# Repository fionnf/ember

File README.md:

# Ember

Two Raspberry Pi Pico W boards keeping their SK6812 RGBW LED strips in sync over MQTT. Touch one lamp and both shift colour together. Control everything from a web app that works on any phone or browser.

---

## Overview

```
[Web UI] ──MQTT (WebSocket)── [board_a / BOSS] ──sync── [board_b / follower]
                                SK6812 strip               SK6812 strip
```

One board (`board_a`, display name **A**) is the BOSS; the other (`board_b`, **B**) is the follower. Both subscribe to the same MQTT topic and keep their strips in sync. The web UI publishes JSON commands to the same topic and reflects live state from both boards.

---

## Hardware

| Part | Notes |
|------|-------|
| Raspberry Pi Pico W (×2) | The W variant — needs WiFi |
| SK6812 RGBW LED strip | 10 LEDs per board, GRBW byte order |
| Data pin | GPIO 5 |
| 300–470 Ω resistor | Series on DIN — prevents ringing |
| 5 V power supply | USB or direct to strip |

### Wiring

```
Pico W GPIO 5 ──[330Ω]──── DIN ────────────── DOUT
5 V / 3.3 V   ─────────── VCC
GND           ─────────── GND

Pico W TOUCH_PIN ──┬──── copper pad / foil
                   └─[1MΩ]── GND
```

> Data flows DIN → DOUT; connect the board's data wire to the **DIN** end of the strip.

If board B connects via the far end (DOUT side), set `REVERSE_LEDS = True` in `config.py` to flip group order in software.

---

## Firmware

### Files

| File | OTA-updated | Purpose |
|------|-------------|---------|
| `boot.py` | Never | OTA bootstrap — downloads firmware from GitHub on every boot |
| `main.py` | Yes | Main loop: WiFi, MQTT, touch, alarms, BOSS sync |
| `colour.py` | Yes | Colour engine: groups, fades, breathing, drift |
| `sk6812.py` | Yes | PIO-based SK6812 RGBW driver |
| `touch.py` | Yes | Capacitive touch detection |
| `config.py` | Never | Per-board constants (never overwritten by OTA) |

### OTA Updates

`boot.py` runs before `main.py` on every boot. It connects to WiFi and downloads the latest `main.py`, `colour.py`, `sk6812.py`, and `touch.py` from the `master` branch of this repo. `config.py` and `boot.py` are never touched. If WiFi is unavailable the board boots from whatever is already on flash.

To update both boards: commit and push to `master`, then click **↺ Reboot Both Boards** in the Settings panel.

Updates are **all-or-nothing**: every file is downloaded and compile-checked before any is installed, so a mid-update network drop can't leave a new `main.py` running against an old `colour.py`.

### Crash-loop rollback

The compile gate rejects firmware that doesn't parse, but valid code can still fail at runtime — a stray function-level `import` once shadowed a module-level one and both boards boot-looped, unreachable until a human pushed a fix. So the boards now keep a way back:

1. `boot.py` increments a counter in `bootfail.txt` on every boot. A **power-on** reset doesn't count — only soft and watchdog resets, which is what a crash loop produces.
2. Once `main.py` has run for a minute it calls `mark_stable()`: the counter is cleared and the running files are promoted to `.ok` backups. Backups are only rewritten when they actually differ, so this costs no flash in steady state.
3. After **3** boots that never reach stability, `boot.py` restores the `.ok` set and skips the update for that one boot — otherwise it would immediately reinstall the firmware that was failing. The lamp comes back on its own in about 15 seconds.
4. The board reports `rolled_back: true` in its heartbeat until it is stable again, so a rejected push is visible rather than silent.

No record is kept of the rejected version: the next scheduled reboot re-downloads `master`, so a pushed fix is picked up with no stale state to clear, and a few quick power cycles can't pin a board to old firmware.

> `boot.py` is **never** updated over the air — a broken bootloader would need USB to recover. Copy it to each board manually once to get this feature (`mpremote connect /dev/ttyACM0 cp boot.py :`).

### Configuration (`config.py`)

```python
BOARD_ID   = "board_a"    # "board_b" on the second Pico
BOSS       = True         # True on board_a only

NUM_LEDS       = 10
LED_PIN        = 5
REVERSE_LEDS   = False

NUM_GROUPS     = 3
GROUP_MIN_LEDS = 1
GROUP_MAX_LEDS = 8

LED_BRIGHTNESS = 0.6
FADE_STEPS     = 60       # steps per colour transition (~1 s at 60 Hz)
BREATHE_SPEED  = 0.0008   # radians/ms
BREATHE_DEPTH  = 0.04     # ±4% brightness oscillation

IDLE_DRIFT_INTERVAL_S = 45

MQTT_BROKER        = "broker.hivemq.com"
MQTT_PORT          = 1883
MQTT_TOPIC_PREFIX  = "ember_CHANGEME"   # ← set to your own unique value

WIFI_NETWORKS = [
    ("YourSSID", "YourPassword"),
]
```

### MQTT

- **Broker:** `broker.hivemq.com:1883` (TCP on device) / `:8884` WSS (web)
- **Events topic:** `<your-prefix>/events`
- **Alarms topic:** `<your-prefix>/alarms` (retained, subscribed by boards)
- **Status topic:** `<your-prefix>/status/<board_id>` (retained, Last-Will)
- **Scenes topic:** `<your-prefix>/scenes` (retained, client-to-client scene library)

All messages are JSON with a `from` field for echo suppression. The full contract is documented in [MQTT Protocol Specification](#mqtt-protocol-specification) — that section is the reference for writing an additional client.

### Colour Engine (`colour.py`)

The `ColourEngine` class manages per-group colour state:

- **Palette position** (`pos`, float 0.0–1.0): maps into a 30-stop hue palette blended with warm white. `0.0` = pure warm white (W channel only); higher values = saturated hues with W fading out.
- **Groups**: the strip is split into 1–N independent colour zones. Each group has a `pos` (hue) and a `w` (warm-white level). Group sizes are stored separately.
- **Fade**: each group independently crossfades from its start colour to its target over `FADE_STEPS` ticks, eased with smoothstep so the transition begins and ends imperceptibly. A fade takes the time it says it does — `fade_steps: 60` really is ~1 s.
- **Breathing**: a per-group sine oscillator adds a slow ±4% brightness pulse with staggered phases.
- **Drift**: optional autonomous colour drift — subtle hue nudges and group-size shifts every `IDLE_DRIFT_INTERVAL_S` seconds. Disabled by default in the web UI (`driftEnabled = false`).
- **Power**: soft on/off with an ~800 ms fade.

### BOSS / Follower Sync

When the BOSS's physical touch sensor fires, it runs `ColourEngine.impulse()` (random colour change), then publishes its new state with `"sync": true`. The follower applies the same groups with a fast fade (`SYNC_FADE_STEPS`) so both strips match immediately.

Every 60 s the BOSS publishes its state with `"sync": true` as a drift-correction heartbeat. The follower applies it with a slow 300-step fade so re-alignment is invisible.

**Independent mode.** That periodic sync would otherwise undo deliberate per-lamp settings — set one lamp with **Send to → B** and it reverted within a minute. So a **targeted** command (one carrying `target`) unlinks the lamps and suppresses the BOSS sync for 30 minutes; a **broadcast** colour command — which sets both lamps to the same thing — re-links them immediately. Boards notice targeted traffic even when it is addressed to the other lamp, so the BOSS knows to stand down.

### Alarms

Each board holds the whole schedule on its own flash (`alarms.json`) and evaluates it against its own clock, so **alarms fire with no client connected**. On each main-loop tick the board compares the current UTC time against enabled alarms and runs:

- **Sunrise** (`type: "sunrise"`): switches on and ramps brightness from 0 to `alarm.brightness` over `duration_min` minutes, sweeping **colour** alongside it — ember red → deep orange → amber → warm white. Because brightness rises together with the colour, the early stops are seen dim and deep, like a real dawn.
- **Bedtime** (`type: "sunset"`): the same sweep in reverse — warm white deepens to ember as it dims — then switches off (restoring the previous brightness so the next power-on isn't dark).

The gradient is `SUNRISE_STOPS` in `colour.py`, deliberately **not** taken from `TINT_PALETTE`: there a single `pos` sets hue and saturation together, so anything warm is also nearly white and a dawn would be an invisible tint.

Stops are evenly spaced by index, so where they sit is what shapes the fade. They are weighted toward the red end: the dawn opens on near-pure red `(255,6,0,0)`, the white LED stays completely dark for the first three fifths, and the turn to warm white happens in the last stretch. Red is never given up — the R channel is full the whole way — so it lands on a warm white with red still under it rather than a cold one. `tests/test_sunrise.py` pins that shape, so the stops stay tunable but the character can't drift back to turning orange almost immediately.

The schedule reaches boards two ways: the **retained** `P/alarms` topic, which boards subscribe to so an offline or rebooting board picks it up on reconnect, and a `set_alarms` message on `P/events` for boards that are already online. Alarms are compared in **UTC**; clients convert local time. See the [protocol spec](#alarms-1) for the exact format.

Two requirements: the board needs a **synced clock** (NTP at boot, retried hourly — the heartbeat's `ntp` field reports this, and the web UI warns when it's false), and it needs to have **received the schedule** (the heartbeat's `alarms` count confirms it). Use the **▶ Test** button on any alarm to run its fade immediately and verify the whole path.

### WiFi Watchdog

If the board loses its MQTT connection (WiFi down or broker unreachable) for more than 10 minutes (`WIFI_OFFLINE_REBOOT_MS = 600000`) it reboots to reconnect and pick up any OTA update. Known networks are the `WIFI_NETWORKS` list in `config.py` plus any saved to `networks.json` on flash, tried in order.

### State Persistence

On/off state and brightness are written to `state.json` and restored on boot before connecting to MQTT — so the lamps come back exactly as they were after the nightly OTA reboot.

Writes are deliberately rationed. The web app includes `on` in every state publish, so persisting on each message meant a flash erase/write on every slider tick (~8 per second while dragging) — needless wear, and each write stalls the render loop. State is now written only when it actually changes: immediately on a power toggle, before any planned reboot, and on a 5-minute flush that bounds what an unexpected power cut can lose.

### Daily OTA reboot

Each board reboots once a day at **17:00 UTC** (`OTA_HOUR_UTC` in `main.py`) to pull the latest firmware. State (on/off + brightness) is saved before the reboot and restored after, so the lamps come back as they were.

### Resilience layers

The firmware is designed to recover from anything without human intervention:

| Layer | Failure it handles |
|-------|--------------------|
| Hardware watchdog (8 s) | Firmware *hangs* — stuck DNS, dead socket, lockup → automatic reboot |
| Crash guard | Any unhandled exception → reboot in 5 s, OTA pulls a fix on the way up |
| OTA compile check | A broken push to master, truncated download, or HTML error page is **refused** — boards keep running the last good firmware |
| All-or-nothing OTA | Every file is downloaded and verified before *any* is installed, so a mid-update network drop can't leave a new `main.py` running against an old `colour.py` |
| Flash-write rationing | State is written only when it changes, so slider drags can't wear out the flash |
| Atomic file writes | Power cut mid-write can't corrupt firmware or state/alarm/network files |
| MQTT input validation | The events topic is on a public broker — every field is validated and clamped before touching the engine or flash; malformed messages are logged and dropped |
| MQTT watchdog | Broker unreachable > 10 min → reboot to re-establish everything |
| NTP retry | Failed clock sync at boot retries hourly (otherwise alarms would silently stay dead until the next reboot) |
| State persistence | On/off + brightness restored after any reboot |
| Periodic GC | Heap stays defragmented over weeks of uptime; free memory is reported in every heartbeat |

The watchdog can be disabled per board (`WATCHDOG_ENABLED = False` in `config.py`) while debugging over WebREPL.

---

## Web UI

`index.html` at the repo root is served via **GitHub Pages**. It connects to the HiveMQ broker over WebSockets. No install required — open it in any browser. On a phone you can **Add to Home Screen** to get it as a standalone full-screen app (web manifest included), and the app automatically reconnects when you return to it after backgrounding.

A service worker (`sw.js`) caches the app shell and the mqtt.js library, so the UI keeps working if the CDN is unreachable. HTML is fetched network-first, so a pushed update always lands rather than stranding you on a cached build.

### Controls

| Control | What it does |
|---------|-------------|
| **Power** | Soft on/off; state reflected in board pills immediately |
| **Tap** | Random colour change (same as physically touching the lamp) |
| **Warm White** | Resets all groups to `pos=0.0, w=1.0` (pure warm white) |
| **Brightness** | Global brightness 0–100% |
| **Fade Speed** | Colour transition duration (~0.3 s–10 s) |
| **Send to** | Target Both boards / A only / B only |

### Strip preview

The top card shows the RGBW strip in real time. Click the small divider cells below the strip to split or merge colour groups.

### Groups

Each group gets a numbered handle on the palette bar — drag it along the hue gradient to pick a colour. The **Warm White** slider below each group blends in warm white independently.

### Alarms

Create sunrise/bedtime alarms per lamp with day-of-week selection, duration, and target brightness.

Times are entered in **your local time**; the small `HH:MM UTC` hint beside each one shows what the lamps actually compare against. Because the firmware only knows UTC, the app stores your intended local time and recomputes the UTC value when needed, so an alarm set for 07:00 stays at 07:00 after a daylight-saving change.

Each alarm has a **▶ Test** button that runs its fade on both lamps immediately (20 s) — the quickest way to confirm the whole path works. A warning banner appears if a lamp's clock hasn't synced, since alarms can't fire without it.

### Scenes

Save and load complete lamp states (colours, group layout, brightness, fade speed).

Scenes are stored in `localStorage` **and** mirrored to the retained `P/scenes` topic, so your phone, your laptop and any other client converge on one shared library. The merge is deliberately conservative — no device can destroy another's work:

- scenes merge by `id`, keeping whichever copy has the newer `updated` stamp
- a scene simply missing from another device's list means "not seen yet", never "delete it"
- deletions travel as **tombstones**, so a deleted scene isn't helpfully synced back by a device that still has it (kept to the last 50)

### Settings panel

| Field | Default | Description |
|-------|---------|-------------|
| WebSocket URL | `wss://broker.hivemq.com:8884/mqtt` | MQTT broker |
| Topic Prefix | randomly generated per install | Must match `MQTT_TOPIC_PREFIX` on the boards |
| LEDs | `10` | LEDs per strip |
| Groups | `3` | Initial group count |

Also: **Add WiFi Network** (sends credentials to both boards over MQTT), **↺ Reboot Both Boards** (triggers OTA update).

### Board presence pills

The two pills (A / B) at the top right show each board's status. Presence uses MQTT **Last-Will** on a retained per-board topic (`prefix/status/<board_id>`): each board publishes `{"online": true}` (retained) on connect, and the broker itself flips it to `{"online": false}` if the board dies silently (within ~90 s of its last keepalive). Because the status is retained, the pills are correct the instant the page loads. The web app additionally pings both boards on connect and every 2 minutes to refresh their full state.

- **Green (online)** — retained status online (or message seen within 150 s) and lights on
- **Amber (standby)** — same, but lights are off
- **No highlight (offline)** — broker reported the board offline, or nothing heard within 150 s

---

## MQTT Protocol Specification

This is the complete contract. Any client (this web app, another web app,
Home Assistant, a script) only needs these topics — there is no other API.

### Topics

With your `MQTT_TOPIC_PREFIX` (call it `P`):

| Topic | Direction | Retained | Payload |
|-------|-----------|----------|---------|
| `P/events` | client ⇄ board | no | Command / state object (below) |
| `P/alarms` | client → board | **yes, QoS 1** | Bare JSON **array** of alarm objects |
| `P/status/<board_id>` | board → client | **yes** | `{"online": bool, "fw": str, "ntp": bool}` |
| `P/scenes` | client ⇄ client | **yes** | Shared scene library (below). Boards ignore it entirely |

Board IDs are `board_a` (BOSS, display name A) and `board_b` (follower, B).

A client should subscribe to `P/events`, `P/alarms`, and `P/status/+`.

### Message envelope (`P/events`)

Every message on `P/events` is a JSON **object**. Non-objects are dropped.

| Field | Type | Meaning |
|-------|------|---------|
| `from` | string | **Required.** Sender ID. A board ignores messages where `from` equals its own ID. IDs starting with `board_` mark board-to-board traffic |
| `target` | string | Optional. If present, only the board with this `board_id` acts on the message |
| `echo` | bool | Optional. Marks an informational state report. **Boards ignore echo-flagged messages** — see below |
| `sync` | bool | Optional. Board-to-board: apply colours with a slow 300-step fade |

> **The `echo` rule matters.** When a board answers a client, it replies with
> its full state plus `"echo": true`. Without that flag the *other* board
> would treat the reply as a real colour change and restart its fade — which
> caused a visible flash on every interaction. If you write a client, never
> set `echo` on commands you send; treat incoming `echo` messages as
> read-only state.

### Commands (client → board, on `P/events`)

All fields are optional; send only what you want to change. Every value is
validated and clamped by the firmware — out-of-range or wrong-typed fields
are ignored, never fatal.

| Field | Type | Range | Effect |
|-------|------|-------|--------|
| `groups` | array | 1…`NUM_LEDS` entries | Per-group colour, below |
| `on` | bool | | Power, with an ~800 ms soft fade |
| `brightness` | number | 0.0–1.0 | Global brightness |
| `fade_steps` | number | 1–2000 | Crossfade length in ~16 ms ticks (60 ≈ 1 s) |
| `drift_enabled` | bool | | Autonomous idle colour drift |
| `drift_interval` | number | 5–86400 | Seconds between drift events |
| `reverse` | bool | | Flip LED order |
| `ping` | any | | Ask boards to reply with their state (`echo: true`) |
| `set_alarms` | array | ≤20 alarms | Install a schedule (see Alarms) |
| `test_alarm` | `"sunrise"` \| `"sunset"` | | Run that fade **immediately** |
| `test_seconds` | number | 2–600 | Duration for `test_alarm` (default 20) |
| `add_network` | object | | `{"ssid": str≤32, "password": str≤64}` — saved to the board's flash |
| `reboot` | truthy | | Save state and restart (triggers an OTA check) |

A `groups` entry:

```json
{"pos": 0.35, "w": 0.8, "size": 3}
```

| Field | Type | Range | Meaning |
|-------|------|-------|---------|
| `pos` | number | 0.0–1.0 | Position in the hue palette. `0.0` = pure warm white (W channel only); higher = saturated tint with W fading out |
| `w` | number | 0.0–1.0 | Warm-white level for this group |
| `size` | integer | ≥1 | How many consecutive LEDs this group covers |

`size` values should sum to `NUM_LEDS`. If they sum to less, the firmware
extends the last group to cover the remainder (so no LED is left showing a
stale colour); if they sum to more, the extra is trimmed. The firmware
resizes its internal group arrays to match the array length, so a per-LED
gradient is simply `NUM_LEDS` groups of `size: 1`.

Example — set three groups and full brightness:

```json
{
  "from": "my_app",
  "groups": [
    {"pos": 0.0,  "w": 1.0, "size": 4},
    {"pos": 0.35, "w": 0.8, "size": 3},
    {"pos": 0.7,  "w": 0.6, "size": 3}
  ],
  "on": true,
  "brightness": 0.6,
  "fade_steps": 60
}
```

### Reports (board → client, on `P/events`)

**State echo** — sent whenever a board acts on a client message (including `ping`):

```json
{
  "from": "board_a", "echo": true,
  "groups": [{"pos": 0.0, "w": 1.0, "size": 10}],
  "on": true, "brightness": 0.6, "fade_steps": 60,
  "drift_enabled": false, "drift_interval": 45
}
```

**Heartbeat** — every 30 s:

```json
{"from": "board_a", "heartbeat": true, "fw": "2026-07-26.5",
 "mem": 102400, "ntp": true, "alarms": 2}
```

| Field | Meaning |
|-------|---------|
| `fw` | Firmware version |
| `mem` | Free heap bytes — watch for leaks |
| `ntp` | **Clock synced?** If `false`, alarms cannot fire — surface this to the user |
| `alarms` | How many alarms the board currently holds — confirms delivery |

**Impulse / boss sync** — a physical touch, or the BOSS's 60 s sync. Same
shape as a state echo but **without** `echo`, so the other board applies it.
Boss syncs carry `"sync": true`.

### Presence (`P/status/<board_id>`, retained)

```json
{"online": true, "fw": "2026-07-26.5", "ntp": true}
```

Registered as the board's MQTT **Last-Will** with payload `{"online": false}`,
so the *broker* publishes the offline state if a board dies silently
(~90 s, from the 60 s keepalive). Because it is retained, a client knows both
boards' state the instant it subscribes — no waiting for a heartbeat.

Recommended client logic: treat `online: false` as authoritative offline;
otherwise consider a board present if `online: true` or a message arrived
within ~150 s. Show offline if your own broker connection is down.

### Alarms

Two transports, both needed:

1. **`P/alarms`, retained, QoS 1** — the durable schedule. Boards subscribe
   to it, so one that was offline or rebooting when the schedule changed
   receives it on reconnect. Payload is a bare JSON **array**.
2. **`{"set_alarms": [...]}` on `P/events`** — the instant path for boards
   that are already online.

Publish **both** on every change, and **never** set `target` on an alarm
update: which lamp acts is decided by the alarm's own `boards` field.

```json
[
  {
    "enabled": true,
    "type": "sunrise",
    "hour": 5,
    "minute": 0,
    "duration_min": 30,
    "brightness": 1.0,
    "days": [0, 1, 2, 3, 4],
    "boards": ["board_a", "board_b"]
  }
]
```

| Field | Type | Range | Meaning |
|-------|------|-------|---------|
| `enabled` | bool | | Skipped when false |
| `type` | string | `sunrise` \| `sunset` | Fade up, or fade down and switch off |
| `hour` | int | 0–23 | **UTC** — see below |
| `minute` | int | 0–59 | **UTC** |
| `duration_min` | int | 1–180 | Ramp length in minutes |
| `brightness` | number | 0.0–1.0 | Sunrise target (ignored for sunset) |
| `days` | int array | 0=Mon … 6=Sun | Omit or send a non-array for *every day* |
| `boards` | string array | board IDs | Which lamps act. Empty/omitted = all |

Each board evaluates the schedule against **its own** UTC clock and runs its
own ramp, so alarms work even with no client connected. At most one alarm
fires per minute per board; a fired alarm is remembered until the next day
(keyed on hour+minute+type, so a sunrise and a sunset at the same time both
fire).

> **Timezone.** The Pico has no timezone database, so the firmware only
> understands UTC. Clients are responsible for converting. This web app edits
> in local time and stores the user's intent in two extra fields, `lh`/`lm`
> (local hour/minute), recomputing `hour`/`minute` on load so alarms keep
> their wall-clock time across a DST change. The firmware ignores `lh`/`lm`.
> **If you write another client, either use the same convention or send UTC
> directly** — and be aware this app will rewrite `hour`/`minute` from
> `lh`/`lm` if both are present.

To verify a schedule without waiting for the clock, send
`{"from": "my_app", "test_alarm": "sunrise", "test_seconds": 20}` — the
board runs the real alarm code path immediately.

### Scenes (retained on `P/scenes`)

Boards ignore this topic entirely; it exists so multiple clients share one
scene library. Publish **retained** so a client that connects later gets it.

```json
{
  "v": 1,
  "from": "web_app",
  "scenes": [
    {
      "id": "lz4f8x-a91b2c",
      "updated": 1774598400000,
      "name": "Evening",
      "groups": [{"pos": 0.0, "w": 1.0, "size": 10}],
      "boundaries": [], "groupPositions": [0.0], "groupWLevels": [1.0],
      "brightness": 0.4, "fadeSteps": 120, "on": true
    }
  ],
  "deleted": ["old-scene-id"]
}
```

| Field | Meaning |
|-------|---------|
| `id` | Stable unique string. **Required** for a scene to take part in sync |
| `updated` | Epoch ms of the last edit — the conflict tiebreak |
| `deleted` | Tombstoned ids, capped at the most recent 50 |

Merge rules (implement these and two clients can't fight):

- union by `id`; on a clash keep the higher `updated`
- a scene absent from the other side means "not seen yet", **not** "delete"
- honour incoming tombstones, and keep publishing your own so a delete
  doesn't get synced back by a device that still holds the scene
- if the merge changed nothing, don't republish — otherwise two clients
  ping-pong retained messages forever

Everything except `id`, `updated` and `name` is opaque payload; this app
stores the fields shown, but another client may store whatever it needs.

### Guarantees for client authors

- Malformed messages are logged and dropped; they never crash a board or
  drop its MQTT connection.
- Unknown fields are ignored, so the protocol can be extended safely.
- Boards persist power state, brightness, and alarms to flash and restore
  them after any reboot.
- The events topic is on a **public broker**. Anyone who knows your prefix
  can control your lamps — pick an unguessable `MQTT_TOPIC_PREFIX`, or run
  your own broker with authentication.

---

## First-Time Setup

1. **Flash MicroPython** — download the Pico W UF2 from micropython.org, hold BOOTSEL, drag it on.

2. **Install umqtt** (in Thonny shell or `mpremote`):
   ```python
   import mip
   mip.install("umqtt.simple")
   ```

3. **Upload files** (only once):
   ```bash
   mpremote connect /dev/ttyACM0 cp boot.py config.py :
   ```
   Set your WiFi credentials in `WIFI_NETWORKS` in the board's `config.py`
   (or create `networks.json` on the board — a list of `[ssid, password]` pairs):
   ```json
   [["YourNetwork", "YourPassword"]]
   ```

4. **Edit `config.py`** — set `BOARD_ID`, `BOSS`, `NUM_LEDS`, `LED_PIN`, `MQTT_TOPIC_PREFIX`.

5. **Reboot** — `boot.py` downloads `main.py`, `colour.py`, `sk6812.py`, `touch.py` from master and starts.

---

## Troubleshooting

| Symptom | Cause | Fix |
|---------|-------|-----|
| Board B LEDs don't light | Connected to DOUT | Run wire to DIN end |
| Wrong colours | Byte-order mismatch | SK6812 uses GRBW — check `sk6812.py` |
| Groups reversed on board B | Far-end connector | `REVERSE_LEDS = True` in `config.py` |
| Touch never fires | Threshold too high | Lower `TOUCH_THRESHOLD` in `config.py` |
| Touch fires constantly | Missing pull-down | 1 MΩ between GPIO and GND |
| Boards not syncing | Different topic prefix | `MQTT_TOPIC_PREFIX` must match on both |
| Board reboots after ~10 min offline | WiFi watchdog | Expected; board reconnects and checks OTA |
| **Alarm fires at the wrong time** | Alarm times are UTC; older clients sent local time as UTC | Times are now edited in local time and converted. Check the small `HH:MM UTC` hint next to each alarm |
| **Alarm never fires** | Board has no clock (NTP failed) | The web UI shows a warning banner; heartbeat `ntp` is false. Retries hourly, or reboot the board |
| **Alarm never fires**, clock is fine | Board never received the schedule | Heartbeat `alarms` count shows 0. Fixed by the retained `P/alarms` topic; press **▶ Test** to confirm the path |
| Alarm only fires on one lamp | Alarm's `boards` list, or a client sending `target` with the update | Enable both lamps on the alarm; never set `target` on alarm updates |
| OTA not updating | `boot.py` not on board | Flash `boot.py` manually once via USB |

---

## Project Structure

```
ember/
├── index.html              # Web UI — single source, served by GitHub Pages
├── sw.js                   # Service worker — caches shell + mqtt.js
├── manifest.json           # PWA manifest (Add to Home Screen)
├── main.py                 # Firmware — main loop (OTA-fetched)
├── colour.py               # Firmware — colour engine (OTA-fetched)
├── sk6812.py               # Firmware — PIO LED driver (OTA-fetched)
├── touch.py                # Firmware — capacitive touch (OTA-fetched)
├── boot.py                 # OTA bootstrap (deployed manually, never overwritten)
├── config.py               # Per-board config TEMPLATE — real credentials live
│                           #   only on the boards, never in the repo
├── hardware_test.py        # Standalone wiring test (no WiFi/MQTT needed)
├── favicon.svg
└── README.md
```

> **Security note:** this repo is public (it serves the web UI via GitHub Pages).
> Never commit real WiFi or WebREPL passwords — edit them only in the `config.py`
> that lives on each board, which OTA never touches.

---

Personal project — no license.

---

## Tests

```bash
python3 tests/test_firmware.py     # boots main(), MQTT commands, flash writes
python3 tests/test_ota.py          # OTA all-or-nothing install
python3 tests/test_rollback.py     # crash-loop rollback
python3 tests/test_sunrise.py      # dawn gradient shape
node    tests/test_scene_sync.js   # scene merge / tombstone rules
```

Runs `main()` against stubbed MicroPython modules (`tests/stubs/`) and checks
that the board boots, arms and feeds the watchdog, subscribes to the events
**and** retained alarms topics, registers its Last-Will, publishes presence and
heartbeats, reboots on command, installs a retained alarm schedule, applies
colour commands, and survives malformed input.

`test_ota.py` drives `boot.py`'s updater against a stubbed HTTP layer and
asserts that a network drop, a syntax error, or an HTTP error part-way
through leaves the existing firmware completely untouched.

Run both before pushing to `master`. `python -m py_compile` only catches syntax
errors — it cannot catch a runtime fault such as a stray function-level
`import`, which once shadowed a module-level import for the whole of `main()`
and put every board into a boot loop.

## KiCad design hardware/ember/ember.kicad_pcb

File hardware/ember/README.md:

# EM-15 rev I — KiCad project

**Ember · EM-15 rev I · © 2026 Fionn Ferreira**
<https://github.com/fionnf/ember>

Generated from [`../../docs/hardware/README.md`](../../docs/hardware/README.md).
Open `fl11.kicad_pcb` with KiCad 9 or 10.

## What changed

**rev B** moved the electronics off the end of the strip into a rear bulge at the middle, so
the USB-C plugs in from the back. **rev C** moved the touch terminals there too: the pad is
now a snap-off section *beside* the bulge, not a tab at the far end.

```
   x=0                                              187
   |<---------- 11 x SK6812 RGBW, unbroken --------->|
   +--------------------------------------------------+
   | (1)(2)(3)(4)(5)(6)(7)(8)(9)(10)(11)  y = 11.000  |
   +----------------+--------------+---+--------------+
        y=20        |  ELECTRONICS |sn |  TOUCH PAD   |
                    |  MCU, power  |ap |  PAD_S       |
                    |  USB-C under |   |  PAD_G       |
              x=72  +--------------+---+--------------+ x=145
                         y=48    x=120 (break + J2/J3)
```

Every wire now leaves the lamp from one place. The board also got **smaller**:

| | rev A | rev B | rev C |
|---|---|---|---|
| Outline | 282 × 20 | 228 × 20 + 48 × 28 | **187 × 20 + 48 × 28 + 25 × 28** |
| Area | 5640 mm² | 5904 mm² | **5784 mm²** (+2.6 % vs A, −2.0 % vs B) |
| SENSE run | 195 mm | ~70 mm | **~13 mm** |
| SENSE crosses the LED data channel | no | yes, once | **no** |

**The real win is SENSE.** §7.5 calls touch "the least-certain subsystem in this design". In
rev A and B the sense line was a long high-impedance run down a strip carrying a 0.89 A
switching rail. In rev C it never leaves the bulge, sits inside the bulge's GND pour — which
*is* the guard — and never crosses the LED data channel. The guarded y=18.6 lane rev B needed
is gone entirely, and so is the awkward climb at x=188.

Deleting the end tab also removed the 31 mm tab, the gap, and the strip's break slot.

**Cost.** Still one bottom-side part (J1), so the second-setup charge stands at roughly
**+$0.63/unit at qty 100**. The outline is a T with a notch, so the 6-up panel still needs
re-nesting and re-quoting.

## rev I — TTP223 module, and the etched sensor is gone

The biggest simplification in the whole design. A **TTP223-class module plugs into J4**
(pin order **IO / VCC / GND**) and does the sensing, which deletes:

- the etched comb electrodes and their whole geometry problem
- the snap-off pad section, the break line, the webs and both bridges
- R10's 4.7 MΩ (now 100 k, a value already on the BOM) — **the thinnest-stock line is gone**
- §7.5's entire uncertainty: the charge-time measurement, the per-unit threshold question,
  the overlay-thickness dependence, the "least-certain subsystem in this design" note

`touch.py` becomes a digital read instead of a timing loop.

**VCC is 3V3, not 5V, deliberately.** These modules drive their output rail-to-rail and the
ESP32-C3 is **not 5V tolerant** (3.6 V absolute max). At 3V3 the output is inherently safe,
and R7's 5.1 kΩ stays in series as belt and braces. `TS3/TS4/TS5` repeat the same three
signals as solder terminals for when no JST housing is to hand.

**Centred geometry.** The LED row sits square on the strip — **15.567 mm of headroom at each
end**, identical. The USB-C sits **dead centre of the bulge at x=98.0**; the module moved
aside to x=115 to make room, which puts its antenna keep-out at y 40.9–46.3 facing the free
y=52 edge, **23.9 mm** from the nearest LED copper against a rule of 8.

**Four screws**: two in the bulge, and one at **each end of the LED strip**, so the full
length is held down rather than just the electronics.

### Routing: complete

| | |
|---|---|
| **Unconnected component pads** | **0** |
| DRC errors | **0** |
| Board | 187 × 20 strip + 64 × 32 bulge, single-sided, 2 layer |
| BOM | 16 lines, 59 placements, 5 BASIC |

Pipeline: `build_fl11.py` places and netlists, `route_fl11.py` lays the pours and the nets
§7.9 insists on by hand, freerouting 2.3.0 finishes the rest through KiCad's Specctra
DSN/SES path, and `finish_routing.py` cleans up after it — width floor, 133 collision-checked
ground vias, solid ties, island removal, stray-pad joins.

## rev G — 15 LEDs, fully routed

**15 LEDs at 11.13333 mm pitch.** The lit zone stays at exactly **167.00 mm** — the lamp
length does not move — and worst-case current drops to **~1.69 A**, back under the 2 A PPTC
hold and inside a 2.4 A supply. F1 returns to the 2 A/4 A part. Both of the warnings rev F
carried (3 A supply, copper resized for 2.25 A) are withdrawn: at 1.69 A the §5.5 sizing
holds with margin.

**The LEDs are warm white.** `C5378724` is `SKC6812RGBW-**WS**` — the WS suffix is warm white.
The neutral-white part is `C5348912` (`-NW`) and would fight `BASE_WARM_WHITE = (0,0,0,200)`,
which is the whole basis of `colour.py`'s model. The BOM note says so explicitly.

### Routing: complete

| | |
|---|---|
| **Unconnected component pads** | **0** |
| DRC errors | 2 (below) |
| Tracks / vias | 345 / 202 — 279 on F.Cu, 66 on B.Cu |
| Copper routed | 865 mm |
| SENSE vias | **0**, as §7.1 requires |

The bulge was finished with **freerouting 2.3.0** driven through KiCad's Specctra DSN/SES
path, then post-processed by `finish_routing.py`. §7.9 says not to autoroute, and that stands
for the three nets it names — so SENSE, the LED chain, the tab bridges and the pours were
hand-routed **first** and the router had to work around them. It did: SENSE still has zero
vias and still never crosses the LED data channel.

`finish_routing.py` then does what the router got wrong: widens its 0.15 mm tracks to the
0.20 mm floor, stitches the ground pours to the plane with 146 collision-checked vias, ties
the priority-3 solid patches that the pour clips around, and removes floating copper islands.

### The two remaining DRC errors — both need a human

1. **`J1.A6` (USB_DP_CONN) vs a USB_DM_CONN track.** This is the 0.5 mm-pitch USB-C fan-out,
   where D+ and D− interleave (`B7 · A6 · A7 · B6` at 0.5 mm). Untangling it needs either a
   via pair under the connector or hand-drawn geometry; it is exactly the case §6.2 means when
   it says route D± by hand.
2. **A STRAP2 via vs a +3V3 track.** A router artifact, a local nudge in KiCad.

Neither is a connectivity failure — every pad is connected. Both are clearance, in the
head area, and both want the PCB editor rather than a script.

## rev F — 20 LEDs

**20 LEDs at 8.33333 mm pitch = 120 LEDs/m**, a standard strip density. Twenty at that pitch
give a lit zone of **exactly 166.67 mm** — the same lamp length as eleven at 60/m, at double
the density, so the dots blend instead of reading individually. The board outline does not
change: LED20 lands at x=168.33 on a 187 mm strip.

**F1 is now 3 A hold / 5 A trip (C18198349).** Twenty LEDs put worst case at **~2.25 A** and a
2 A hold would nuisance-trip. Same 1812 footprint, no layout change.

**Two consequences you must not skip:**

- **The supply must be 3 A**, not the 2.4 A the §9.2 budget assumed. Or cap `MAX_CHANNEL_SUM`
  in firmware — at 20 LEDs the old 680 value no longer keeps you under 2 A.
- **The copper was sized for 1.6 A** (§5.5). The 4.6 mm 5 V pour probably carries 2.5 A at an
  acceptable rise, but that calculation has not been redone and must be before ordering.

`NUM_LEDS` becomes 20 in `config.py`. The bypass caps moved to y=15.10 rotated 0: at 8.33 mm
pitch a vertical 0402 could not sit inside the 4.6 mm pour with room for thermal spokes.

### Routing status — checked, not assumed

| | |
|---|---|
| DRC | **0 errors** |
| LED chain | **all 19 DOUT→DIN hops routed** |
| LED power/ground | all 20 LEDs and all 20 bypass caps connected |
| SENSE, touch pad, tab terminals | routed |
| **Unrouted** | **54 endpoints, all in the bulge** — power path, USB pair, module I/O, J4 |

Two routing bugs were found and fixed getting here, both silent: the hop loop was still bounded
at 11 so **LEDs 11–20 had no data connection**, and the bypass caps' 5 V pads sat too close to
the pour edge for thermal spokes, leaving 23 of them floating. Neither showed up as a DRC error
— they only appear in the unconnected count, which is why that number is quoted here.

## rev E

**Interdigitated touch electrodes.** Two solid plates couple mostly through the overlay's
thickness. A comb pushes the field *out* of the surface as fringing, which is what a finger
behind plastic actually intercepts — so sensitivity through a thin cover goes up sharply and
degrades gracefully as the cover thickens. Finger pitch is 3.0 mm with 1.1 mm fingers, so a
~10 mm fingertip always spans several SENSE/GND pairs. Seven fingers per electrode, a SENSE
spine at the break edge and a GND spine plus return bar, still with no copper on B.Cu beneath.

**J4 — commercial-sensor fallback.** Four pads (`5V`, `3V3`, `GND`, `SIG`) beside the break.
If the etched sensor ever disappoints, a TTP223-class module wires straight in: it needs a
supply, a ground and one digital output, and `TOUCH_GPIO` doubles as that input because
`touch.py`'s pin is plain digital, not ADC. Both supply rails are brought out because those
modules come in 3.3 V and 5 V variants. Zero placements, zero BOM lines.

**Silkscreen.** Version, `© 2026 Fionn Ferreira` and the repo URL, with the copyright
repeated on the snap-off pad so it stays identified after the break. This was claimed in the
rev C and rev D commit messages but the calls had been lost in an earlier edit and were not
actually on the board — they are now.

## rev D

Three changes, all from real problems:

**Back to single-sided.** J1 is a *horizontal* receptacle, so the plug enters along the board
plane from the rear edge whichever face it is soldered to. Bottom-mounting it bought
flushness and cost a whole second assembly setup. It is on the top side now: rear entry
unchanged, **the ~$0.63/unit second-setup charge is gone**, and the CPL has zero bottom-side
parts.

**The pad section could not actually snap off.** In rev C it touched the rest of the board on
*two* edges — the bulge at x=120 and the strip along y=20 — and only the first was cut. It now
hangs off the bulge alone: the strip is notched away over y 20–22, so the pad is cantilevered
and can be gripped and bent. Retaining material is two 1.3 mm webs carrying SENSE and GND plus
two 0.4 mm corner ligaments, **≈3.0 mm against rev C's 4.3 mm on two separate edges.** Webs are
1.3 mm rather than narrower because a 0.30 mm trace needs 0.5 mm to each routed edge; below
that the fab flags it.

**The BOM carries real LCSC numbers.** Blank part numbers are what made JLC guess, and its
guess for the 100 k line was C880433 — an **01005** part, Extended, 6 in stock, MOQ 5597. Every
line is now filled from a live stock check, favouring Basic/Preferred with deep stock.

| Line | Part | Why |
|---|---|---|
| 100 nF ×15 | **C1525** | Basic, 16.4 M stock |
| 5k1 ×7 | **C25905** | Basic, 2.24 M stock |
| 100 k ×2 | **C25086** | Preferred, 469 k stock — *not* the 01005 JLC suggested |
| 100 R | **C22369194** | 1.13 M stock, 5 % — tolerance is irrelevant for series damping |
| 22 µF ×4 | **C6119897** | Preferred, 184 k, **$0.02 vs $0.12** for the 25 V Basic part |
| 4M7 | **C49655641** | Extended, **only ~9.8 k stock** — buy in one PO |
| 470 µF | **C47023096** | 7.4 k stock, D8 × 10.5 mm |
| USBLC6 | **C2687116** | 150 k stock |
| AP2112K-3.3 | **C23380830** | 31 k stock |
| Tact | **C18078117** | 20.5 k stock |
| Module | **C2838502** | 26 k stock, **$3.84 — the doc modelled $2.92** |

Two still need you: **F1 (PPTC 1812, 2 A hold / 4 A trip, ≤0.06 Ω)** is not filled — I could not
verify one, so it is blank rather than guessed. And **the LED, C5378724, is unverified for
stock** and is §9.1's number one live risk.

**Two cost corrections, both upward:** the module is ~$0.9/board dearer than modelled, and with
more Extended lines than the doc's assumed five, the fixed charge `8.18 + 1.53 + 3.07 × N`
rises — roughly +$0.30/board at qty 30. Against that, single-sided gives back ~$0.63/unit.

**22 µF derating:** the 10 V part loses roughly half its capacitance at 5 V DC bias, so budget
~10–12 µF effective. That is fine here — C1's 470 µF carries the bulk and C4 only has to cover a
2 ms burst — but it is a real difference from the nameplate value.

## Status — read before ordering

**Not yet orderable.** Placed, netlisted, poured, partly routed.

| | |
|---|---|
| Footprints | 67, DRC **0 errors** |
| Nets | 35, every pad assigned |
| Routed | LED chain, buffer→LD1, SENSE end-to-end, tab electrodes, bypass vias, all pours |
| **Not routed** | **51 connections in the bulge** — power path, USB pair, module I/O |

Reproduce: `kicad-cli pcb drc --format json --severity-error --refill-zones fl11.kicad_pcb`

## Deviations from the written design, and why

| Change | Reason |
|---|---|
| **R11 is 100 Ω, was 47 Ω** | §6.6 sized 47 Ω for a 12 mm buffer→LD1 run and argued the trace is electrically short. In rev B that run is **~80 mm**, past the doc's own ~75 mm critical length, so it now needs real series termination: AHCT Zout 15–25 Ω + ~120 Ω trace ≈ 100 Ω. |
| **Touch pad beside the bulge, end tab deleted** | rev C. Puts the wire terminals with the rest of the wiring and cuts SENSE from ~70 mm to ~13 mm. It no longer crosses the LED data channel — which mattered, because *every* x between LEDs carries a DOUT→DIN hop, so rev B had to climb at x=188, past LD11_DOUT's end, as the only legal crossing point. |
| **Touch pad electrodes 17 × 12 mm** (204 mm² each), was 25 × 8 | Same area as §7.5 specifies, reproportioned for a pad section that is tall rather than long. Equal areas are still correct: `C ∝ s(A−s)/A` maximises at `s = A/2`. |
| **Cross-section mirrored** (GND at y=0 side, 5 V under the LED anodes) | The LED package puts VDD and DIN on the same side, so head-to-tab data flow forces VDD to the y=20 side. Also makes the doc self-consistent: §7.2's caps at y=15.50 only work if 5 V is the bottom band. |
| **H1/H2 in the bulge**, not flanking J1 | An M2.5 screw head does not fit beside a 16-pin USB-C receptacle (courtyard x 0.69–10.20, y 4.63–15.37) on a 20 mm board. |
| **Mouse-bite webs at y=8.73 and 11.27**, 1.8 mm wide | Exactly where SENSE and GND cross the break line. The "centre bridge" needs material under the traces. |
| **LEDs at 90°** | The rotation that gives DIN-left / DOUT-right, so no two hops cross. Verify pad 1 against the LCSC drawing — §6.6 flags a rotated LED row as a scrap panel. |

## Still to do, in §7.9 order

1. Route VBUS → F1 → Q1 → star node → 5 V into the bulge pour, clearing the antenna keep-out.
2. Route D+/D− as a 90 Ω pair through U4 to IO18/IO19 — matched within 5 mm, no vias.
3. Route 3V3, EN, straps, IO9/SW1.
4. Stitching vias; silkscreen for the break block and `CUT -> D1`.
5. Re-nest the panel around the bulge and re-quote.

Do not autoroute.

## Provenance of the module pad map

`U1`'s footprint and pin numbering come from **Espressif's official KiCad library**, not from
me — §6.5 explicitly refused to invent the ESP32-C3-MINI-1 pad map. Cross-check against the
datasheet before ordering.

## Regenerating

```
python3 build_fl11.py fl11.kicad_pcb <Espressif.pretty> c3_padmap.json
python3 route_fl11.py fl11.kicad_pcb
```
Needs KiCad's bundled Python. Zone filling is done by `kicad-cli --refill-zones`, because
`ZONE_FILLER` segfaults without a wxApp. Two other API traps are noted in the scripts:
a footprint must be added to the board *before* `Flip()`, and `SetOutline()` does not take
ownership of the polygon.

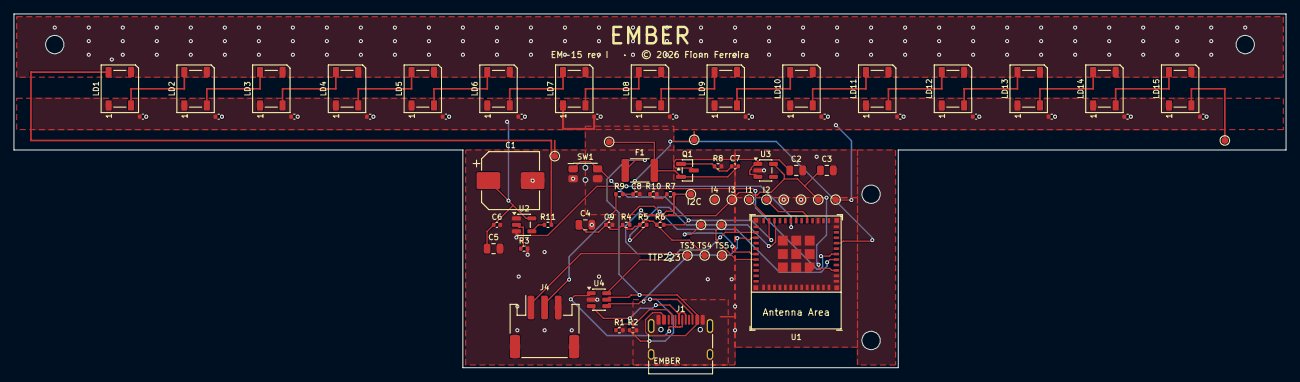
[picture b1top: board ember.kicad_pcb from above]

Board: 2 copper layers, 187.0 x 52.0 mm, 81 parts (0 on the bottom side), 41 nets.

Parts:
C1: 470uF/10V; CP_Elec_8x10
C2, C3, C4, C5: 22uF; C_0805_2012Metric
C6, C7, C8, C9, C10, C11, C12, C13, C14, C15, C16, C17, C18, C19, C20, C21, C22, C23, C24: 100nF; C_0402_1005Metric
F1: PPTC 2A/4A; R_1812_4532Metric
H1, H2, H3, H4: M2.5; MountingHole_2.7mm_M2.5
I1: I2C_SDA; TestPoint_Pad_D1.0mm
I2: I2C_SCL; TestPoint_Pad_D1.0mm
I3: +3V3; TestPoint_Pad_D1.0mm
I4: GND; TestPoint_Pad_D1.0mm
J1: USB-C 16P; USB_C_Receptacle_HRO_TYPE-C-31-M-12
J4: IO/VCC/GND; JST_PH_S3B-PH-SM4-TB_1x03-1MP_P2.00mm_Horizontal
LD1, LD2, LD3, LD4, LD5, LD6, LD7, LD8, LD9, LD10, LD11, LD12, LD13, LD14, LD15: SK6812RGBW; LED_WS2812B_PLCC4_5.0x5.0mm_P3.2mm
Q1: AO3401A; SOT-23
R1, R2, R3, R4, R5, R6, R7: 5k1; R_0402_1005Metric
R8, R9, R10: 100k; R_0402_1005Metric
R11: 100R; R_0402_1005Metric
SW1: BOOT; SW_SPST_EVQP7C
TP1: LED_5V; TestPoint_Pad_D1.0mm
TP2: +3V3; TestPoint_Pad_D1.0mm
TP3, TP4: GND; TestPoint_Pad_D1.0mm
TP5: LED_DIN1; TestPoint_Pad_D1.0mm
TP6: TOUCH_SENSE; TestPoint_Pad_D1.0mm
TP7: LD11_DOUT; TestPoint_Pad_D1.0mm
TP8: UART_TX; TestPoint_Pad_D1.0mm
TP9: UART_RX; TestPoint_Pad_D1.0mm
TP10: EN; TestPoint_Pad_D1.0mm
TP11: VBUS_F; TestPoint_Pad_D1.0mm
TS3: TOUCH_SENSE; TestPoint_Pad_D1.0mm
TS4: +3V3; TestPoint_Pad_D1.0mm
TS5: GND; TestPoint_Pad_D1.0mm
U1: ESP32-C3-MINI-1-N4; ESP32-C3-MINI-1
U2: SN74AHCT1G125; SOT-23-5
U3: AP2112K-3.3; SOT-23-5
U4: USBLC6-2SC6; SOT-23-6

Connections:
+3V3: C3.1, C4.1, C9.1, I3.1, J4.2, R4.1, R5.1, R6.1, R9.1, TP2.1, TS4.1, U1.3, U3.5
+5V: C2.1, Q1.3, U3.1, U3.3
BOOT_N: R6.2, SW1.1, U1.23
CC1: J1.A5, R1.1
CC2: J1.B5, R2.1
D_1_2: LD1.2, LD2.4
D_2_3: LD2.2, LD3.4
D_3_4: LD3.2, LD4.4
D_4_5: LD4.2, LD5.4
D_5_6: LD5.2, LD6.4
D_6_7: LD6.2, LD7.4
D_7_8: LD7.2, LD8.4
D_8_9: LD8.2, LD9.4
D_9_10: LD9.2, LD10.4
D_10_11: LD10.2, LD11.4
D_11_12: LD11.2, LD12.4
D_12_13: LD12.2, LD13.4
D_13_14: LD13.2, LD14.4
D_14_15: LD14.2, LD15.4
EN: C8.1, R9.2, TP10.1, U1.8
GATE: C7.1, Q1.1, R8.1
GND: C1.2, C2.2, C3.2, C4.2, C5.2, C6.2, C8.2, C9.2, C10.2, C11.2, C12.2, C13.2, C14.2, C15.2, C16.2, C17.2, C18.2, C19.2, C20.2, C21.2, C22.2, C23.2, C24.2, I4.1, J1.A1, J1.A12, J1.B1, J1.B12, J1.SH, J4.3, J4.MP, LD1.3, LD2.3, LD3.3, LD4.3, LD5.3, LD6.3, LD7.3, LD8.3, LD9.3, LD10.3, LD11.3, LD12.3, LD13.3, LD14.3, LD15.3, R1.2, R2.2, R3.2, R8.2, R10.2, SW1.2, TP3.1, TP4.1, TS5.1, U1.1, U1.2, U1.11, U1.14, U1.36, U1.37, U1.38, U1.39, U1.40, U1.41, U1.42, U1.43, U1.44, U1.45, U1.46, U1.47, U1.48, U1.49, U1.50, U1.51, U1.52, U1.53, U2.1, U2.3, U3.2, U4.2
I2C_SCL: I2.1, U1.16
I2C_SDA: I1.1, U1.18
LD11_DOUT: LD15.2, TP7.1
LED_5V: C1.1, C5.1, C6.1, C10.1, C11.1, C12.1, C13.1, C14.1, C15.1, C16.1, C17.1, C18.1, C19.1, C20.1, C21.1, C22.1, C23.1, C24.1, LD1.1, LD2.1, LD3.1, LD4.1, LD5.1, LD6.1, LD7.1, LD8.1, LD9.1, LD10.1, LD11.1, LD12.1, LD13.1, LD14.1, LD15.1, TP1.1, U2.5
LED_DATA_3V3: R3.1, U1.19, U2.2
LED_DATA_5V: R11.1, U2.4
LED_DIN1: LD1.4, R11.2, TP5.1
STRAP2: R4.2, U1.5
STRAP8: R5.2, U1.22
TOUCH_GPIO: R7.1, R10.1, U1.6
TOUCH_SENSE: J4.1, R7.2, TP6.1, TS3.1
UART_RX: TP9.1, U1.30
UART_TX: TP8.1, U1.31
USB_DM: U1.26, U4.6
USB_DM_CONN: J1.A7, J1.B7, U4.1
USB_DP: U1.27, U4.4
USB_DP_CONN: J1.A6, J1.B6, U4.3
VBUS_F: C7.2, F1.2, Q1.2, TP11.1
VBUS_RAW: F1.1, J1.A4, J1.A9, J1.B4, J1.B9, U4.5

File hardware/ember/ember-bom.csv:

Comment,Designator,Footprint,LCSC Part #,Note
470uF/10V,C1,CP_Elec_8x10,C47023096,"Extended. 7.4k stock, D8 x 10.5mm - thinnest stock on the board after the LED"
22uF,"C2,C3,C4,C5",C_0805_2012Metric,C6119897,"0805 10V X5R, 184k stock, $0.020 vs $0.119 for the 25V BASIC part C45783 - the single biggest safe saving on the board, $0.39/unit across four places. DC bias at 5V derates it to ~10-12uF effective, which is fine here: the LDO needs >=1uF, and C1's 470uF carries the bulk"
100nF,"C6,C7,C8,C9,C10,C11,C12,C13,C14,C15,C16,C17,C18,C19,C20,C21,C22,C23,C24",C_0402_1005Metric,C1525,"BASIC. 16.4M stock, 16V X7R"
PPTC 2A/4A,F1,R_1812_4532Metric,C883156,"Extended. BSMD1812-200-16V, 2A hold / 4A trip, 76k stock - the section 6.2 spec. At 15 LEDs worst case is ~1.69 A"
USB-C 16P,J1,USB_C_Receptacle_HRO_TYPE-C-31-M-12,C165948,"HRO TYPE-C-31-M-12, 90k stock, $0.186. The $0.087 GT-USB-7010ASV was rejected: its footprint has 0.175 mm copper-to-hole, under JLC's 0.25 mm minimum. TOP side, plug enters from the rear board edge"
IO/VCC/GND,J4,JST_PH_S3B-PH-SM4-TB_1x03-1MP_P2.00mm_Horizontal,C7429690,"ZX-PH2.0-WT3P, 3-pin 2.0mm right-angle SMD, 17k stock, $0.053. Genuine JST S3B-PH-SM4-TB is C265101 at $0.377 if the clone footprint disappoints - CHECK the chosen part's drawing against the JST land pattern before ordering"
SK6812RGBW,"LD1,LD2,LD3,LD4,LD5,LD6,LD7,LD8,LD9,LD10,LD11,LD12,LD13,LD14,LD15",LED_WS2812B_PLCC4_5.0x5.0mm_P3.2mm,C5378724,"SKC6812RGBW-WS = WARM WHITE (the -NW suffix, C5348912, is neutral and would fight BASE_WARM_WHITE). *** STOCK NOT VERIFIED - section 9.1 number one live risk. 4-channel RGBW, GRBW order. An RGB part fits the same footprint and is silently wrong ***"
AO3401A,Q1,SOT-23,C15127,"P-FET. Source to INPUT side, drain to load"
5k1,"R1,R2,R3,R4,R5,R6,R7",R_0402_1005Metric,C25905,"BASIC. 8.4M stock, 1%"
100k,"R8,R9,R10",R_0402_1005Metric,C25741,"BASIC. 15.4M stock, 1%. Replaces C25086 - JLC now lists that Extended, 0 stock, MOQ 700"
100R,R11,R_0402_1005Metric,C25076,BASIC. 9.8M stock
BOOT,SW1,SW_SPST_EVQP7C,C49234124,"3x4x2mm SMD tact, 101k stock, $0.019 - half the price of C18078117 with 5x the stock"
ESP32-C3-MINI-1-N4,U1,ESP32-C3-MINI-1,C2838502,"Extended. 26k stock, $3.84 - doc modelled $2.92, budget ~$0.9/board more"
SN74AHCT1G125,U2,SOT-23-5,C7484,AHCT/HCT ONLY. C7468 is AHC and fixes nothing - two digits apart
AP2112K-3.3,U3,SOT-23-5,C23380830,"Extended. 31k stock. EN ties to VIN, not VOUT"
USBLC6-2SC6,U4,SOT-23-6,C2687116,Extended. 150k stock

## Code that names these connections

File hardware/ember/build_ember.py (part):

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    return nets[name]
for n in ["I2C_SDA","I2C_SCL","GND","VBUS_RAW","VBUS_F","+5V","LED_5V","+3V3","GATE","EN","CC1","CC2",
          "USB_DP_CONN","USB_DM_CONN","USB_DP","USB_DM","LED_DATA_3V3","LED_DATA_5V",
          "LED_DIN1","LD11_DOUT","TOUCH_GPIO","TOUCH_SENSE","BOOT_N","STRAP2","STRAP8",
          "UART_TX","UART_RX"]: N(n)
for i in range(1,NLED): N(f"D_{i}_{i+1}")

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 ("C6","1"):"LED_5V", ("C6","2"):"GND", ("C5","1"):"LED_5V", ("C5","2"):"GND",
 ("R3","1"):"LED_DATA_3V3", ("R3","2"):"GND",
 ("R11","1"):"LED_DATA_5V", ("R11","2"):"LED_DIN1",
 ("R10","1"):"TOUCH_GPIO", ("R10","2"):"GND",
 ("R7","1"):"TOUCH_GPIO", ("R7","2"):"TOUCH_SENSE",
 ("R4","1"):"+3V3", ("R4","2"):"STRAP2", ("R5","1"):"+3V3", ("R5","2"):"STRAP8",
 ("R6","1"):"+3V3", ("R6","2"):"BOOT_N",
 ("SW1","1"):"BOOT_N", ("SW1","2"):"GND",
}
PAD = json.load(open(PADMAP))
for sig, net in (("IO4","I2C_SDA"),("IO10","I2C_SCL"),("IO5","LED_DATA_3V3"),("IO3","TOUCH_GPIO"),("IO2","STRAP2"),
                 ("IO8","STRAP8"),("IO9","BOOT_N"),("IO18","USB_DM"),("IO19","USB_DP"),
                 ("IO20","UART_RX"),("IO21","UART_TX"),("EN","EN"),("3V3","+3V3")):
    CONN[("U1", PAD[sig])] = net
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
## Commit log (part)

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2026-04-15 Add: smoke test
2026-05-12 Fix: Connection issues
2026-05-12 Add: Readme for remote control
2026-05-12 Add: more colour options
2026-05-12 Tweak: Adjust animation timing parameters
2026-05-13 Add: Support for precise group state updates and MQTT keepalive
    Refactored `force_colour` to handle detailed group-level state updates. Enhanced MQTT client with exponential reconnect backoff and periodic pings to maintain keepalive.
2026-05-13 Add: Enhanced control features and idle drift synchronization via MQTT
    Expanded ColourEngine with brightness, reverse, fade steps, and drift controls. Integrated board-targeted MQTT messaging and synchronized idle drift impulses across boards.
2026-05-13 Remove .claude worktree from tracking, add .gitignore
2026-05-13 Add index.html to root for GitHub Pages
2026-05-13 Disable Jekyll for GitHub Pages
2026-05-13 Add Zurück zu Gacha button
2026-05-13 Add boot.py OTA updater — pulls latest code from GitHub on boot
2026-05-13 Move REVERSE_LEDS to config.py as a proper setting
2026-05-13 Add WiFi network management: save via MQTT, persist to networks.json, add network form in web app
2026-05-13 Add scenes: save, load, delete with colour preview swatches
2026-05-13 Make auto drift subtle: tiny hue nudges, occasional ±1 LED resize, slow fade
2026-05-13 Remove: Boot pulse logic for simplified startup sequence
    Removed the pulsing LED feedback and associated code from `boot.py` to streamline the boot process and reduce complexity. Adjusted delays and related logic accordingly.
2026-05-13 Add customizable board IDs and names with pill label updates
    Introduced configurable IDs and labels for boards A and B in both `index.html` files and settings. Enhanced `updatePills` to reflect dynamic names and improved related configurations, storage, and re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
2026-05-17 Fix multiple interface bugs: drift default, scene echo loop, button states
    - Drift now defaults OFF (was incorrectly ON)
    - Fix MQTT scene receive loop: receiving scenes no longer re-publishes to
    broker, which was overwriting newer saved scenes with stale retained data
    - Remove auto-publishState on connect: was resetting boards to warm-white
    defaults every time the web app connected or reconnected
    - Disable animation tiles, Apply button, and Save to Board button when
2026-05-17 Fix second round of interface bugs: connectivity guards, status display, dead code
    - Add btn-reboot and btn-add-network to disabled-on-disconnect list
    - btn-add-network toast now reflects actual connectivity
    - Board lib Play/Delete buttons guard against disconnected state (Play was
    showing ✓ when nothing was sent; Delete was removing locally but board
    still had the animation and it would come back on reconnect)
    - Fix publishRetained in reconnect handler: was calling on the old client
2026-05-18 Fix: Capture anim_params in scenes for custom animations
    Custom animation scenes weren't saving their animation parameters
    (pattern, hue_start, hue_end, sync), so loading them would lose the
    custom settings. Now captureScene() includes anim_params when the
    animation mode is 'custom'.
    https://claude.ai/code/session_01GJTYQ4srFbxVTdvm6KLU67
2026-05-18 Improve UI/UX: Add scrolling, hover effects, and zoom interactions
    Enhanced the interface for better usability when there are many items:
    - Added max-height and scrolling to scenes list (300px), board library (300px),
    and alarms list (400px) to prevent layout issues with many items
    - Custom scrollbar styling for smooth appearance across lists
    - LED strip preview scrollable horizontally for high LED counts
    - Improved hover effects with subtle translate and scale animations on:
2026-05-18 Polish UI interactions: Enhanced hover effects on all interactive elements
    Added smooth animations and visual feedback to improve tactile feel:
    - Animation tiles now lift on hover with shadow
    - Control pills and buttons have subtle elevation on hover
    - Pattern buttons show background change on hover
    - Power and tap buttons have enhanced shadow effects
    - Group panel swatches scale slightly on group panel hover
2026-05-18 Add organic, smooth animations with cubic-bezier easing
    Replaced linear transitions with cubic-bezier easing curves for more natural,
    springy interactions that feel responsive and alive:
    - Used cubic-bezier(0.34, 1.56, 0.64, 1) for scale/transform transitions
    - Increased animation durations slightly (0.2s) for smoother feel
    - Enhanced shadow effects with stronger gradients on hover
    - Added keyframe animations for gentle-bounce and smooth-glow
2026-05-18 Add mobile-responsive design for screens < 640px
    Optimized layout and spacing for smaller screens:
    - Reduced padding and margins on mobile
    - Animation grid reduced to 4 columns (640px) and 3 columns (480px)
    - Smaller LED preview and divider cells for mobile
    - Adjusted button and control sizes for touch
    - Reduced scroll container heights on mobile
2026-05-18 Implement press-and-hold power button with 280ms duration and design improvements
    - Replace simple click listener with comprehensive touch/mouse event handling
    - Add visual feedback with 'held' class (scale 0.95, inset shadow)
    - Support both quick click and press-and-hold toggle modes
    - Add smooth-glow animation on MQTT connect status indicator
    - Improve board pill styling with cubic-bezier hover effects
    - Add max-height constraints with scrolling to scene list, board library, alarms
2026-05-18 Optimize for mobile performance
    - Disable smooth-glow animations on screens ≤800px
    - Reduce hover effect complexity on touch devices
    - Simplify cubic-bezier animations to linear transitions
    - Reduce box-shadow complexity on hover states
    - Remove transform animations (scale, translateY) on small screens
    - Optimize animation frame rate: 20fps on mobile, 30fps on desktop
2026-05-18 Fix 5 bugs: static rainbow overflow, custom scene UI sync, anim loop background drain, alarm slider publish flood, randomise max group size
    - Static Rainbow: capped at 12 groups max (was creating one group per LED,
    flooding palette bar and group panels with 100+ elements at high LED counts)
    - Custom scene load: added syncCustomAnimUI() to update pattern buttons, sync
    toggle, and hue range handles when loading a scene — they were silently stale
    - Also sync custom UI when receiving anim_params from MQTT
    - Animation loop: pause via visibilitychange when tab is hidden, resume on return
2026-05-18 Cap max LEDs at 10
2026-05-18 Smoother UX: PWA meta, haptic power toggle, Enter-to-save inputs, disconnect toast, fix hover jank
    - Add PWA meta tags (theme-color, apple-mobile-web-app-capable) for cleaner
    homescreen install and status bar on iOS
    - Haptic feedback on power toggle (navigator.vibrate(20)) on supported devices
    - Enter key saves on scene name, board lib name, and custom animation name inputs
    - Show toast 'Connection lost' when MQTT drops after a successful connection,
    rather than silently updating the status dot
2026-05-19 Performance: in-place LED updates, cache DOM refs, stop anim loop when off, smarter MQTT sync
    - Palette drag: replace renderStrip() with _updateLedColorsInPlace() on every
    mousemove — was destroying and rebuilding all LED DOM nodes on every pixel
    of drag; now just updates background colors of existing elements
    - Cache palette bar element on first drag instead of getElementById every move
    - _ledColour: accept pre-computed customP param; _animFrame computes it once
    per frame instead of allocating a new object per LED per frame
2026-05-20 Fix 3 bugs: hue drag on mobile, numGroups clamp, anim flicker during palette drag
    - Hue range handles: change touchstart to { passive: false } and call
    e.preventDefault() so the browser doesn't start scrolling before
    the drag gesture is established on mobile
    - numGroups: clamp to [1, 10] on load and on reconnect — an out-of-range
    value (0, empty string, huge number) would cause division by zero in
    getGroups() or hang the browser recreating thousands of DOM nodes
